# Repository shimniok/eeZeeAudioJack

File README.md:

Breadboard breakout for 3.5mm stereo audio jack with detect switch on each pin.

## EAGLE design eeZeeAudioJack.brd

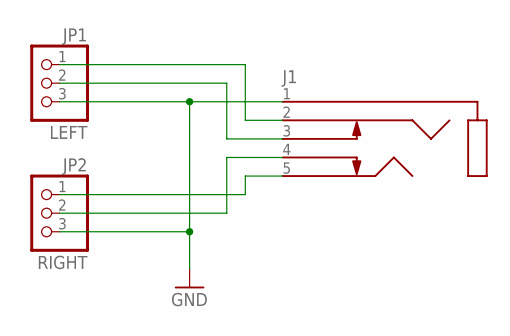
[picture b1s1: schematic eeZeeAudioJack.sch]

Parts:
J1: STEREO_JACK3F07; 3.5AUDIO_3F07
JP1: LEFT; 1X03-S
JP2: RIGHT; 1X03-S

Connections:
GND: J1.1 (SLEEVE), JP1.3, JP2.3
RING: J1.5 (RING), JP2.1
RING_SW: J1.4 (RSWITCH), JP2.2
TIP: J1.2 (TIP), JP1.1
TIP_SW: J1.3 (TSWITCH), JP1.2

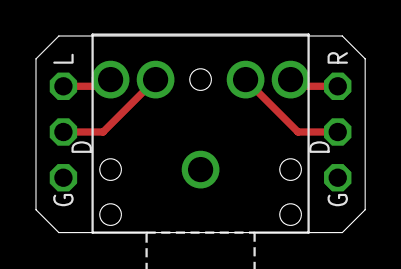
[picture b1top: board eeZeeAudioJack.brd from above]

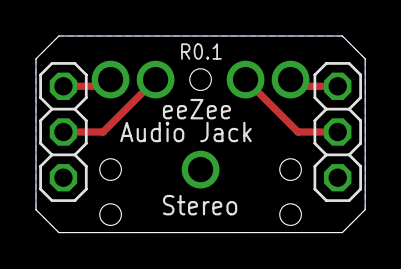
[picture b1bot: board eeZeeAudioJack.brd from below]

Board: 2 copper layers, 18.3 x 10.9 mm, 3 parts (2 on the bottom side), 5 nets.

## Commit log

2015-09-28 initial revision
2015-09-28 Added README
